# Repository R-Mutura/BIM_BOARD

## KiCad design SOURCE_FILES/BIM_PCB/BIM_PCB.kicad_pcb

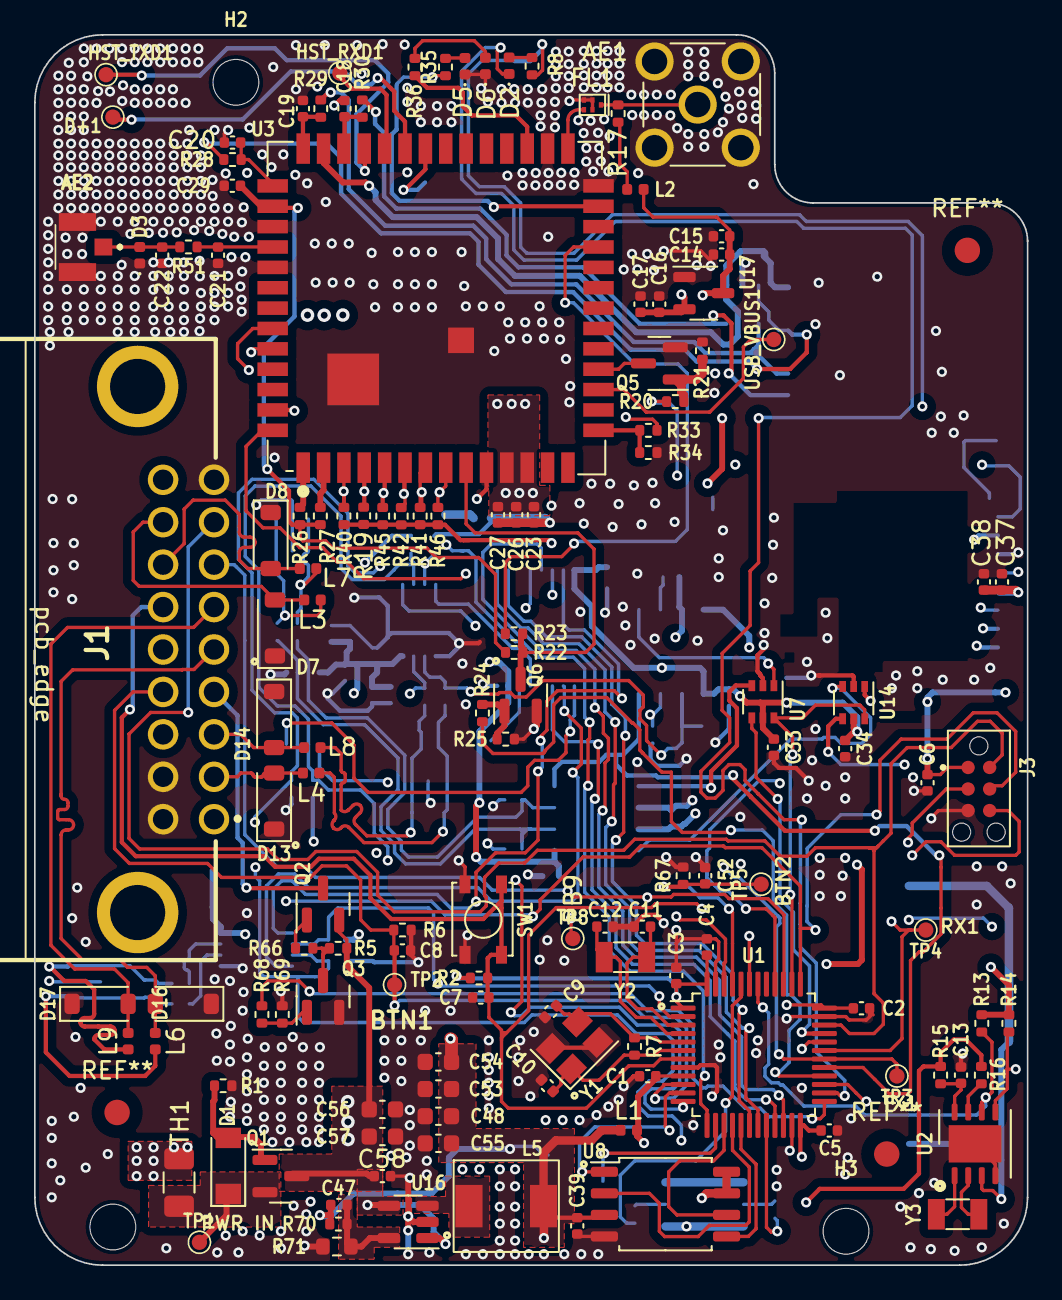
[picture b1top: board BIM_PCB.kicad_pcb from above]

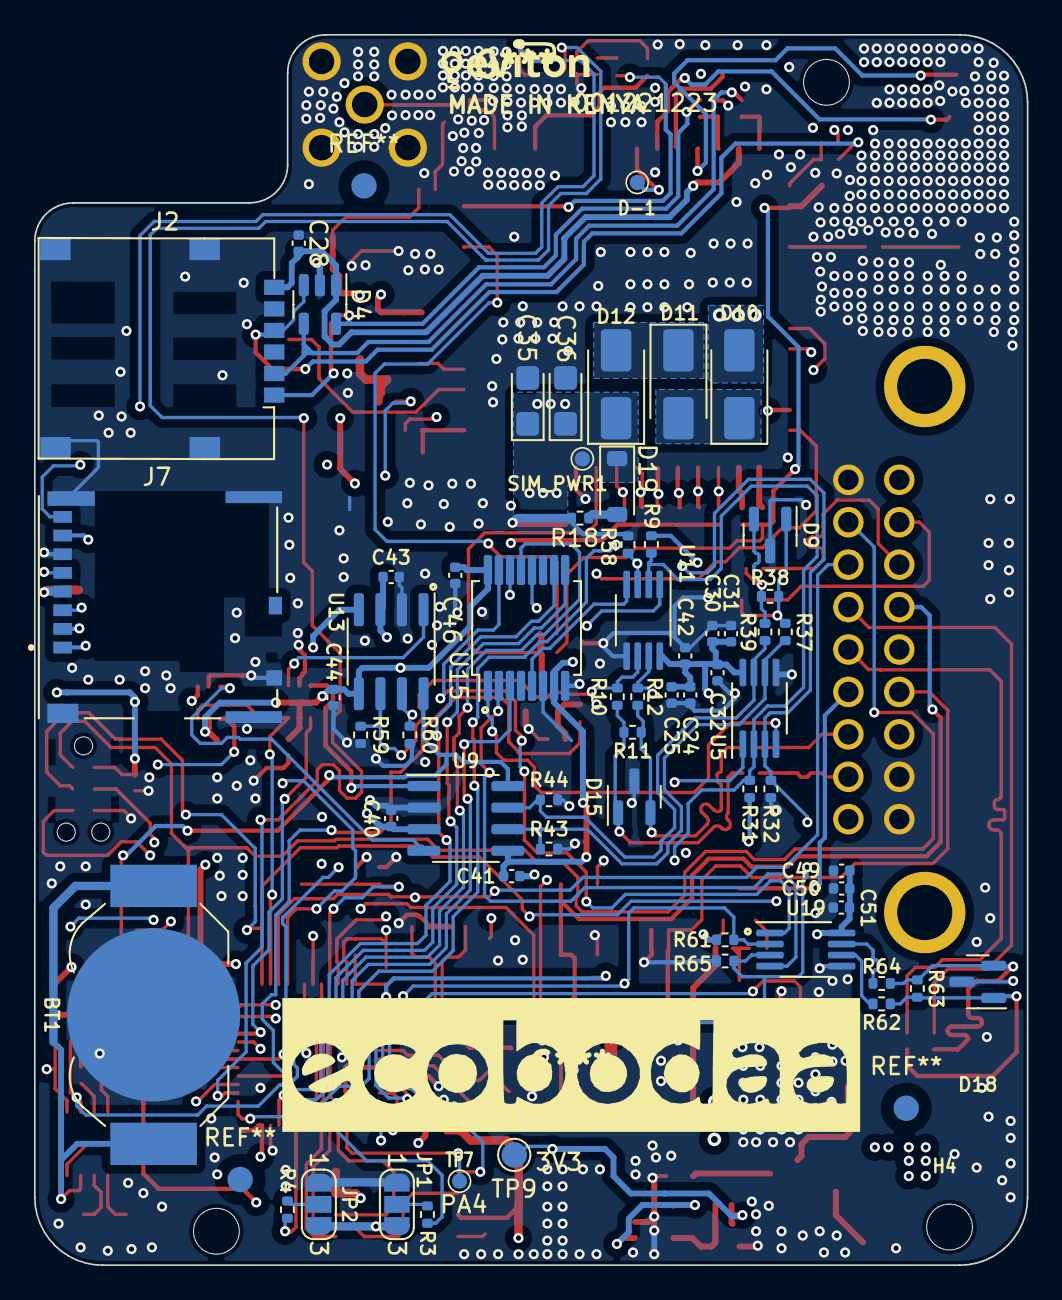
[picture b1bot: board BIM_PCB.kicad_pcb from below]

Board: 4 copper layers, 58.5 x 72.5 mm, 197 parts (63 on the bottom side), 129 nets.

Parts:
AE1: Antenna_Shield; SMA_Molex_73251-2200_Horizontal
AE2: Antenna_Shield; UFL_COAX_CONN23370191
BT1: Battery_Cell; BatteryHolder_LINX_BAT-HLD-012-SMT
C1, C2, C3, C4, C5, C7, C8, C24, C25, C30, C31, C33, C34, C39, C40, C41, C43, C44, C46, C49, C50, C52, C58: 100n; C_0402_1005Metric
C6, C15, C17, C23, C29, C38: 1u; C_0402_1005Metric
C9, C10, C11, C12, C18, C19, C20: 22p; C_0402_1005Metric
C13, C26, C27, C32, C42, C51: 10u; C_0402_1005Metric
C14, C16, C28, C37: 0.1u; C_0402_1005Metric
C21, C22: C_Small; C_0402_1005Metric
C35, C36: 100u; CP_EIA-3216-18_Kemet-A
C47: 8.2p; C_0402_1005Metric
C48: 10n; C_0603_1608Metric
C53: 33p; C_0603_1608Metric
C54: 10p; C_0603_1608Metric
C55: 22u; C_0603_1608Metric
C56, C57: 10u; C_0603_1608Metric
D1: MMSZ5232B-E3-08; D_SOD-123
D2: LED; LED_0402_1005Metric
D3: LXES15AAA1-153; D_0402_1005Metric
D4: SP0504BAHT; SOT-23-5
D5: ORANGE; LED_0402_1005Metric
D6: BLUE; LED_0402_1005Metric
D7, D8, D13, D14, D16, D17: BEP0080MA; D_SOD-123
D9, D15, D18: ESDONCAN1LT1G; SOT-23
D10: RS1K-E3/5ATSS310; D_SMA
D11, D12: SS310; D_SMA
D19: 4.4-4.5 ZENER; D_SOD-123
D+1: D+; TestPoint_Pad_D0.9mm
D-1: D-; TestPoint_Pad_D0.9mm
FL1: SAFEB1G57KE0F00R15; Filter_1411-5_1.4x1.1mm
H2, H3, H4: MountingHole; MountingHole_2.7mm
HST_RXD1: HST_RXD; TestPoint_Pad_D0.9mm
HST_TXD1: HST_TXD; TestPoint_Pad_D0.9mm
J1: Conn_02x09_Counter_Clockwise; conn_18pin_02x09_angled_MX23A18NF1
J2: nano_sim; nano_sim_NSIM-2-C
J3: Conn_01x06; J-LINK_6-PIN_NEEDLE_ADAPTER
J7: Micro_SD_Card; MOLEX_503398-1892
JP1: BOOT0; SolderJumper-3_P1.3mm_Open_RoundedPad1.0x1.5mm_NumberLabels
JP2: BOOT1; SolderJumper-3_P1.3mm_Open_RoundedPad1.0x1.5mm_NumberLabels
L1: L_Ferrite; L_0402_1005Metric
L2: 82nH; L_0402_1005Metric
L3, L4, L6, L7, L8, L9: ferrite bead; L_0402_1005Metric
L5: 2.2u; MDA5030-100M
Q1, Q2: SSM3J328R-HXY; SOT-23
Q3, Q5, Q6: IRLML0100TRPBF; SOT-23
R1, R18: 49.9R; R_0402_1005Metric
R2, R5, R6, R21, R22, R25, R67, R69: 10K; R_0402_1005Metric
R3, R4, R9, R31, R32, R34, R58, R61, R65: 100K; R_0402_1005Metric
R7: 1M; R_0402_1005Metric
R8: 499R; R_0402_1005Metric
R10, R12, R37, R39, R62, R64: 10R; R_0402_1005Metric
R11, R15, R38, R63: 220R; R_0402_1005Metric
R13, R14, R16: 4.7K; R_0402_1005Metric
R17, R28, R29, R30: 22R; R_0402_1005Metric
R19, R40, R41, R42, R45, R46: 10k; R_0402_1005Metric
R20, R23, R24, R66: 1k; R_0402_1005Metric
R26, R27: 2.2K; R_0402_1005Metric
R33: 200K; R_0402_1005Metric
R35, R36: 390R; R_0402_1005Metric
R43, R44, R59, R60: 60R; R_0402_1005Metric
R51: 0R; R_0402_1005Metric
R68: 100R; R_0402_1005Metric
R70: 180K; R_0402_1005Metric
R71: 40K; R_0603_1608Metric
SIM_PWR1: TestPoint; TestPoint_Pad_D0.9mm
SW1: reset; SKRPACE010
TH1: Thermistor_PTC; Fuse_1206_3216Metric
TP1, TP3, TP4: TestPoint; TestPoint_Pad_D0.9mm
TP2: BTN; TestPoint_Pad_D0.9mm
TP5: BTN2; TestPoint_Pad_D0.9mm
TP7: PA4; TestPoint_Pad_D0.9mm
TP8: PB9; TestPoint_Pad_D0.9mm
TP9: TestPoint; TestPoint_Pad_D1.5mm
U1: STM32F103C8Tx; LQFP-48_7x7mm_P0.5mm
U2: PCF8523TK; HVSON-8-1EP_4x4mm_P0.8mm_EP2.2x3.1mm
U3: A9G_MODULE
U5, U11, U19: SSP3485U; MSOP-8_3x3mm_P0.65mm
U7, U14: SN74LVC1G3157DBVR; SOT-363_SC-70-6
U8: W25Q32JVSS; SOIC-8_5.23x5.23mm_P1.27mm
U9, U13: ATA6561-GAQW-N; SOIC-8_3.9x4.9mm_P1.27mm
U15: MC74HC4052A; SSOP-16_5.3x6.2mm_P0.65mm
U16: SY8089AAAC; SOT-23-5
U17: XC6206PxxxMR; SOT-23-3
USB_VBUS1: USB_VBUS; TestPoint_Pad_D0.9mm
Y1: 8MHz; Crystal_SMD_3225-4Pin_3.2x2.5mm
Y2, Y3: 32.678KHz; Crystal_SMD_3215-2Pin_3.2x1.5mm

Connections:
2V8: C16.1, C17.1, C37.1, C38.1, J7.4 (VDD), R19.1, R40.1, R41.1, R42.1, R45.1, R46.1, U17.2 (VO)
4.2V_SIMPWR: C14.1, C15.1, C23.1, C26.1, C27.1, C35.1, C36.1, D12.1 (K), D19.1 (K), L2.2, R33.2, SIM_PWR1.1, U3.11 (VBAT), U3.12 (VBAT), U17.3 (VI)
+3.3VA: C24.1, C25.1, C30.1, C31.1, C32.1, C42.1, C49.1, C50.1, C51.1, R9.2, R31.2, R61.2, U5.8 (VCC), U11.8 (VCC), U19.8 (VCC)
+3V3: C33.1, C34.1, C39.1, C41.1, C44.1, C46.1, C47.1, C48.1, C53.1, C54.1, C55.1, L1.1, L5.2, R15.2, R16.2, R70.1, TP9.1, U7.5 (VCC), U8.3 (IO2), U8.7 (IO3), U8.8 (VCC), U9.5 (NSIL), U13.5 (NSIL), U14.5 (VCC), U15.7 (VEE), U15.16 (VCC)
+5V: C40.1, C43.1, C56.1, C57.1, C58.1, D10.2 (A), Q1.3 (D), Q2.2 (S), R5.1, U9.3 (VCC), U13.3 (VCC), U16.1 (EN), U16.4 (IN)
/A9G_GSM_GPRS_MODULE/GPRS_NET-STATUS: R35.1, U3.26 (IO27)
/A9G_GSM_GPRS_MODULE/GPS POSITION: R36.1, U3.30 (IO28)
/A9G_GSM_GPRS_MODULE/GPS_RXD: U1.12 (PA2), U3.50 (UART2_RXD/IO5)
/A9G_GSM_GPRS_MODULE/GPS_TXD: U1.13 (PA3), U3.49 (UART2_TXD/IO4)
/A9G_GSM_GPRS_MODULE/IO29: R23.1, U3.24 (IO29)
/A9G_GSM_GPRS_MODULE/PWRKEY: R24.1, U1.28 (PB15)
/A9G_GSM_GPRS_MODULE/Sim_CLK: C19.1, R29.1, U3.41 (SIM_CLK)
/A9G_GSM_GPRS_MODULE/Sim_DIO: C18.1, R30.1, U3.39 (SIM_DIO)
/A9G_GSM_GPRS_MODULE/Sim_RST: C20.1, R28.1, U3.42 (SIM_RST)
/A9G_GSM_GPRS_MODULE/Sim_Restart: R20.1, U1.40 (PB4)
/A9G_GSM_GPRS_MODULE/TF_CARD_CONN/SD_CLK: J7.5 (CLK), R46.2, U3.8 (SD_CLK/SPI1_CLK/I2C1_SCL/IO8)
/A9G_GSM_GPRS_MODULE/TF_CARD_CONN/SD_CMD: J7.3 (CMD), R41.2, U3.7 (SD_CMD/SPI1_SC0/I2C1_SDA/IO9)
/A9G_GSM_GPRS_MODULE/TF_CARD_CONN/SD_D0: J7.7 (DAT0), R42.2, U3.6 (SD_D0/SPI1_CSI/IO10)
/A9G_GSM_GPRS_MODULE/TF_CARD_CONN/SD_D1: J7.8 (DAT1), R45.2, U3.5 (SD_D1/SPI1_D0/IO11)
/A9G_GSM_GPRS_MODULE/TF_CARD_CONN/SD_D2: J7.1 (DAT2), R19.2, U3.4 (SD_D2/SPI1_DI/IO12)
/A9G_GSM_GPRS_MODULE/TF_CARD_CONN/SD_D3: J7.2 (DAT3/CD), R40.2, U3.3 (SD_D3/IO13)
/A9G_GSM_GPRS_MODULE/VIO: C29.1, R22.2, R26.2, R27.2, U3.43 (VIO)
/A9G_GSM_GPRS_MODULE/V_Sim: C28.2, D4.1 (K), J2.C1 (VCC), U3.40 (VSIM)
/BUTTON: C8.1, J1.13, R6.1, TP2.1, U1.10 (PA0)
/Button_2: C52.1, J1.14, R67.1, TP5.1, U1.45 (PB8)
/CAN_RX_2: U9.4 (RXD), U14.3 (B0)
/CAN_STBY: U1.29 (PA8), U9.8 (STBY), U13.8 (STBY)
/CAN_TRANSCEIVER_ATA6561/A_to_CANL: R37.1, R43.1, U5.6 (A), U9.6 (CANL)
/CAN_TRANSCEIVER_ATA6561/B_to_CANH: R39.1, R44.1, U5.7 (B), U9.7 (CANH)
/CAN_TRANSCEIVER_ATA6562/A_to_CANL: R10.1, R59.1, U11.6 (A), U13.6 (CANL)
/CAN_TRANSCEIVER_ATA6562/B_to_CANH: R12.1, R60.1, U11.7 (B), U13.7 (CANH)
/CAN_TX_2: U7.3 (B0), U9.1 (TXD)
/DISPLAY_PWR_EN: R68.2, U1.25 (PB12)
/DISPLAY_RS485_DI: U15.2 (Y2), U19.4 (DI)
/DISPLAY_RS485_RO: U15.15 (X2), U19.1 (RO)
/DIS_A: D16.2 (A2), J1.5, L6.2
/DIS_B: D17.2 (A2), J1.6, L9.2
/ECU_A: D13.2 (A2), J1.2, L4.2
/ECU_B: D14.2 (A2), J1.3, L8.2
/FLASH_MEMORY/CS: U1.11 (PA1), U8.1 (~CS)
/FLASH_MEMORY/MISO: U1.16 (PA6), U8.2 (DO(IO1))
/FLASH_MEMORY/MOSI: U1.17 (PA7), U8.5 (DI(IO0))
/FLASH_MEMORY/SCK: U1.15 (PA5), U8.6 (CLK)
/MULTIPLEXER_SWITCH_WAS3157B-6/SEL: U1.38 (PA15), U7.6 (SEL), U14.6 (SEL)
/MULTIPLEXER_SWITCH_WAS3157B-6/SIG1_IN: U1.33 (PA12), U7.4 (A/COM)
/MULTIPLEXER_SWITCH_WAS3157B-6/SIG2_IN: U1.32 (PA11), U14.4 (A/COM)
/MUX_SEL_A: U1.18 (PB0), U15.10 (A)
/MUX_SEL_B: U1.19 (PB1), U15.9 (B)
/RESET: C7.1, J1.15, J3.3, R2.2, SW1.2, U1.7 (NRST)
/RS485_A: D7.2 (A2), J1.17, L3.2
/RS485_B: D8.2 (A2), J1.16, L7.2
/RS485_D1: U5.4 (DI), U15.1 (Y0)
/RS485_DE: R32.2, R58.2, R65.2, U1.27 (PB14), U5.3 (DE), U11.3 (DE), U19.3 (DE)
/RS485_MAX487/A_to_CANL: R62.1, U19.6 (A)
/RS485_MAX487/B_to_CANH: R64.1, U19.7 (B)
/RS485_RO: U5.1 (RO), U15.12 (X0)
/RS485_~RE: R9.1, R31.1, R61.1, U1.2 (PC13), U5.2 (~RE), U11.2 (~RE), U19.2 (~RE)
/RTC_MODULE_IC_PCF8523/RTC_~INT: R16.1, U2.7 (~INT1/CLKOUT)
/SCL: R13.1, U1.42 (PB6), U2.6 (SCL)
/SDA: R14.1, U1.43 (PB7), U2.5 (SDA)
/STM32FC8T6_MCU/3v3_stm: C1.1, C2.1, C3.1, C4.1, C5.1, C6.1, J3.1, JP1.3 (B), JP2.3 (B), L1.2, R2.1, R8.1, R13.2, R14.2, U1.1 (VBAT), U1.9 (VDDA), U1.24 (VDD), U1.36 (VDD), U1.48 (VDD)
/STM32FC8T6_MCU/BOOT0: R3.1, U1.44 (BOOT0)
/STM32FC8T6_MCU/BOOT1: R4.2, U1.20 (PB2)
/STM32FC8T6_MCU/RS485_DI: U1.21 (PB10), U15.3 (Y)
/STM32FC8T6_MCU/RS485_RO: U1.22 (PB11), U15.13 (X)
/STM32FC8T6_MCU/RX1: TP4.1, U1.31 (PA10), U3.54 (UART1_TXD/IO1)
/STM32FC8T6_MCU/TX1: TP3.1, U1.30 (PA9), U3.53 (UART1_RXD/IO0)
/STM32FC8T6_MCU/xtal_1: C11.2, U1.3 (PC14), Y2.2
/STM32FC8T6_MCU/xtal_2: C12.2, U1.4 (PC15), Y2.1
/STM32FC8T6_MCU/xtal_in: C9.2, R7.1, U1.5 (PD0), Y1.3
/STM32FC8T6_MCU/xtal_out: C10.2, R7.2, U1.6 (PD1), Y1.1
/SW0: J1.7, J3.6, U1.39 (PB3)
/ecu_CAN_RX_2: U13.4 (RXD), U14.1 (B1)
/ecu_CAN_TX_2: U7.1 (B1), U13.1 (TXD)
/ecu_RS485_DI: U11.4 (DI), U15.5 (Y1)
/ecu_RS485_RO: U11.1 (RO), U15.14 (X1)
/swdclk: J1.12, J3.4, U1.37 (PA14)
/swdio: J1.8, J3.2, U1.34 (PA13)
GND: AE1.2 (Shield), AE2.2 (Shield), BT1.2 (-), C1.2, C2.2, C3.2, C4.2, C5.2, C6.2, C7.2, C8.2, C9.1, C10.1, C11.1, C12.1, C13.2, C14.2, C15.2, C16.2, C17.2, C18.2, C19.2, C20.2, C21.1, C22.1, C23.2, C24.2, C25.2, C26.2, C27.2, C28.1, C29.2, C30.2, C31.2, C32.2, C33.2, C34.2, C35.2, C36.2, C37.2, C38.2, C39.2, C40.2, C41.2, C42.2, C43.2, C44.2, C46.2, C48.2, C49.2, C50.2, C51.2, C52.2, C53.2, C54.2, C55.2, C56.2, C57.2, C58.2, D3.1 (A1), D4.2 (A), D5.1 (K), D6.1 (K), D7.1 (A1), D8.1 (A1), D9.3 (A), D13.1 (A1), D14.1 (A1), D15.3 (A), D16.1 (A1), D17.1 (A1), D18.3 (A), FL1.2, FL1.3, FL1.5, J1.9, J1.10, J1.11, J2.C5 (GND), J2.MP1, J3.5, J7.6 (VSS), J7.9 (SHIELD), JP1.1 (A), JP2.1 (A), Q3.2 (S), Q5.2 (S), Q6.2 (S), R1.2, R6.2, R18.2, R21.1, R25.1, R32.1, R34.1, R43.2, R44.2, R58.1, R59.2, R60.2, R65.1, R67.2, R69.2, R71.2, SW1.1, U1.8 (VSSA), U1.23 (VSS), U1.35 (VSS), U1.47 (VSS), U2.4 (VSS), U2.9 (VSS), U3.10 (GND), U3.27 (GND), U3.29 (GND), U3.44 (GND), U3.46 (GND), U3.55 (GND), U3.56 (GND), U5.5 (GND), U7.2 (GND), U8.4 (GND), U9.2 (GND), U11.5 (GND), U13.2 (GND), U14.2 (GND), U15.6 (ENABLE), U15.8 (GND), U16.2 (GND), U17.1 (GND), U19.5 (GND), Y1.2, Y1.4
unnamed: AE1.1 (A), FL1.1, R17.2
unnamed: AE2.1 (A), C22.2, D3.2 (A2), R51.2
unnamed: BT1.1 (+), U2.3 (VBAT)
unnamed: D1.2 (A), Q1.1 (G), R1.1
unnamed: D1.1 (K), Q1.2 (S), TH1.2, TP1.1
unnamed: D2.2 (A), R8.2
unnamed: D2.1 (K), U1.26 (PB13)
unnamed: D5.2 (A), R35.2
unnamed: D6.2 (A), R36.2
unnamed: D9.1 (K), L3.1, R37.2, R38.2
unnamed: D9.2 (K), L7.1, R38.1, R39.2
unnamed: D10.1 (K), D11.2 (A)
unnamed: D11.1 (K), D12.2 (A)
unnamed: D15.1 (K), L4.1, R10.2, R11.2
unnamed: D15.2 (K), L8.1, R11.1, R12.2
unnamed: D18.1 (K), L6.1, R62.2, R63.2
unnamed: D18.2 (K), L9.1, R63.1, R64.2
unnamed: D19.2 (A), R18.1
unnamed: J1.4, Q2.3 (D)
unnamed: D4.4 (K), J2.C3 (CLK), R29.2
unnamed: D4.5 (K), J2.C7 (I/O), R30.2
unnamed: D4.3 (K), J2.C2 (RST), R28.2
unnamed: JP1.2 (C), R3.2
unnamed: JP2.2 (C), R4.1
unnamed: L2.1, R17.1
unnamed: Q2.1 (G), R66.2
unnamed: Q3.3 (D), R5.2, R66.1
unnamed: Q3.1 (G), R68.1, R69.1
unnamed: Q5.3 (D), U3.18 (RESET)
unnamed: Q5.1 (G), R20.2, R21.2
unnamed: Q6.3 (D), R22.1, R23.2, U3.9 (PWR_KEY)
unnamed: Q6.1 (G), R24.2, R25.2
unnamed: TP7.1, U1.14 (PA4)
unnamed: TP8.1, U1.46 (PB9)
unnamed: U2.1 (OSCI), Y3.2
unnamed: U2.2 (OSCO), Y3.1
unnamed: C13.1, R15.1, U2.8 (VDD)
unnamed: R33.1, R34.2, U3.15 (ADC0)
unnamed: FL1.4, U3.28 (GPS_RF)
unnamed: C21.2, R51.1, U3.45 (GSM_RF)
unnamed: HST_TXD1.1, U3.38 (HST_RXD)
unnamed: HST_RXD1.1, U3.37 (HST_TXD)
unnamed: R26.1, U3.1 (I2C2_SCL/IO19)
unnamed: R27.1, U3.2 (I2C2_SDA/IO20)
unnamed: D-1.1, U3.35 (USB_N)
unnamed: D+1.1, U3.36 (USB_P)
unnamed: U3.17 (VUSB_DET), USB_VBUS1.1
unnamed: C47.2, R70.2, R71.1, U16.5 (FB)
unnamed: L5.1, U16.3 (LX)
VIN: J1.1, J1.18, TH1.1

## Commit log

2023-12-07 updates on schematic and complete layout
2023-12-10 completed design PCN and Images
2023-12-11 complete BIM Board
2023-12-12 small updates
2023-12-12 updates on the buck 3v3 supply
2023-12-12 bom updates
2023-12-17 update to A9G and connector
2023-12-18 updated step
2023-12-18 updated GENERAL
2023-12-21 xmas
2024-01-13 completed gerber and placement
2024-01-16 updates in BOM gerber and PCL
2024-01-16 completed project
2024-01-17 completed BIM board- ECOBoda
2024-01-23 completed project and all the prouction files
2024-01-28 all items updated
2024-01-28 all items updated including fiducial
2024-02-07 BIM updated BOM and placement files guide pdf added
